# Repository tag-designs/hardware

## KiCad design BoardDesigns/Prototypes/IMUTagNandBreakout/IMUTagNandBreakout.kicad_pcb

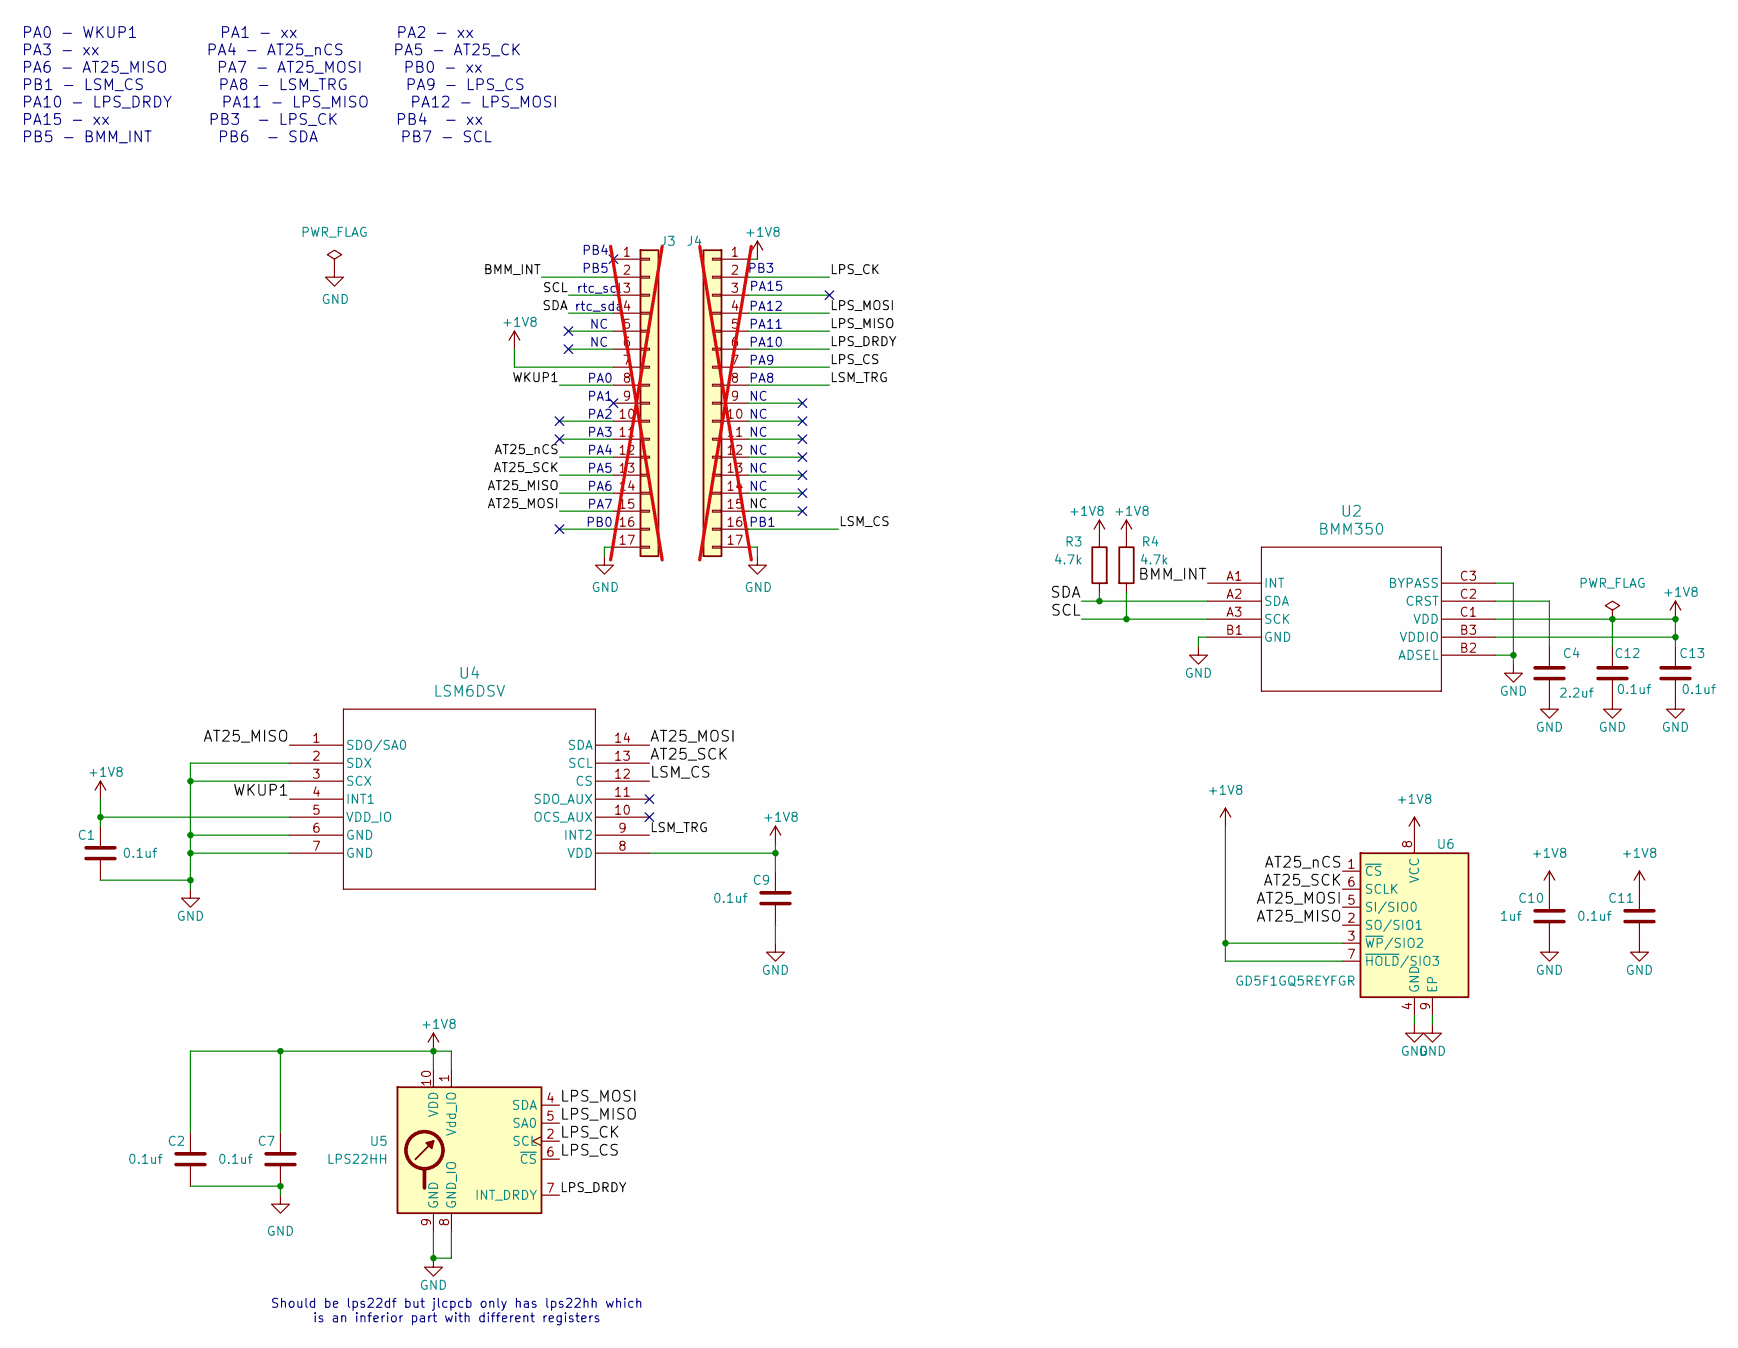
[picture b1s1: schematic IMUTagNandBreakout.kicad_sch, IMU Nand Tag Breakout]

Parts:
C1, C2, C7, C9, C11, C12, C13: 0.1uf; C_0603_1608Metric; MPN CC0603KRX7R9BB104; LCSC C14663
C4: 2.2uf; C_0603_1608Metric; MPN GRM188R61H225KE11D; LCSC C162273
C10: 1uf; C_0603_1608Metric; MPN CL10A105KB8NNNC; LCSC C15849
J3, J4: Conn_01x17; PinHeader_1x17_P2.54mm_Vertical_Staggered; not fitted
R3, R4: 4.7k; R_0603_1608Metric; MPN 0603WAF4701T5E; LCSC C23162
U2: BMM350; BGA9_BMM350_BOS; MPN BMM350; LCSC C17225907
U4: LSM6DSV; LGA14-L_2P59X3P1X0P5_STM; MPN LSM6DSV; LCSC C5267406
U5: LPS22HH; ST_HLGA-10_2x2mm_P0.5mm_LayoutBorder3x2y; MPN LPS22HH; LCSC C2827824
U6: GD5F1GQ5REYFGR; WSON-8-1EP_8x6mm_P1.27mm_EP3.4x4.3mm; MPN GD5F1GQ5REYFGR; LCSC C2976330

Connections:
+1V8: C1.1, C2.1, C7.1, C9.1, C10.1, C11.1, C12.1, C13.1, J3.7, J4.1, R3.1, R4.1, U2.B3 (VDDIO), U2.C1 (VDD), U4.5 (VDD_IO), U4.8 (VDD), U5.1 (Vdd_IO), U5.10 (VDD), U6.3 (~WP/SIO2), U6.7 (~HOLD/SIO3), U6.8 (VCC)
/AT25_MISO: J3.14, U4.1 (SDO/SA0), U6.2 (SO/SIO1)
/AT25_MOSI: J3.15, U4.14 (SDA), U6.5 (SI/SIO0)
/AT25_SCK: J3.13, U4.13 (SCL), U6.6 (SCLK)
/AT25_nCS: J3.12, U6.1 (~CS)
/BMM_INT: J3.2, U2.A1 (INT)
/LPS_CK: J4.2, U5.2 (SCL)
/LPS_CS: J4.7, U5.6 (~CS)
/LPS_DRDY: J4.6, U5.7 (INT_DRDY)
/LPS_MISO: J4.5, U5.5 (SA0)
/LPS_MOSI: J4.4, U5.4 (SDA)
/LSM_CS: J4.16, U4.12 (CS)
/LSM_TRG: J4.8, U4.9 (INT2)
/NC: J4.15
/SCL: J3.3, R4.2, U2.A3 (SCK)
/SDA: J3.4, R3.2, U2.A2 (SDA)
/WKUP1: J3.8, U4.4 (INT1)
GND: C1.2, C2.2, C4.2, C7.2, C9.2, C10.2, C11.2, C12.2, C13.2, J3.17, J4.17, U2.B1 (GND), U2.B2 (ADSEL), U2.C3 (BYPASS), U4.2 (SDX), U4.3 (SCX), U4.6 (GND), U4.7 (GND), U5.3 (GND), U5.8 (GND_IO), U5.9 (GND), U6.4 (GND), U6.9 (EP)
unnamed: C4.1, U2.C2 (CRST)

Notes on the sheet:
PA1
PA9
PA2
PA0
PA8
PA7
PA15
PA5
PA4
PB3
PA6
Should be lps22df but jlcpcb only has lps22hh which is an inferior part with different registers
PA3
PA0 - WKUP1 PA1 - xx PA2 - xx PA3 - xx PA4 - AT25_nCS PA5 - AT25_CK PA6 - AT25_MISO PA7 - AT25_MOSI PB0 - xx PB1 - LSM_CS PA8 - LSM_TRG PA9 - LPS_CS PA10 - LPS_DRDY PA11 - LPS_MISO PA12 - LPS_MOSI PA15 - xx PB3 - LPS_CK PB4 - xx PB5 - BMM_INT PB6 - SDA PB7 - SCL
PB4
PA12
PB0
PB5
PA10
rtc_sda
PA11
PB1
rtc_scl

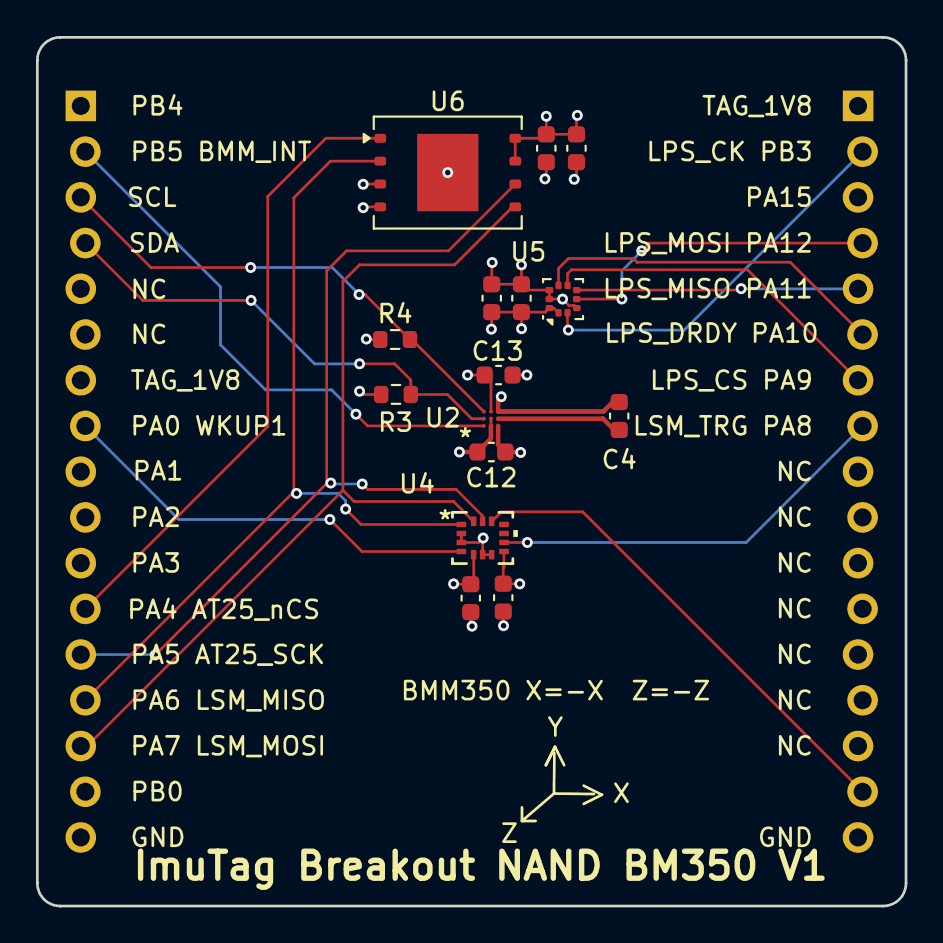
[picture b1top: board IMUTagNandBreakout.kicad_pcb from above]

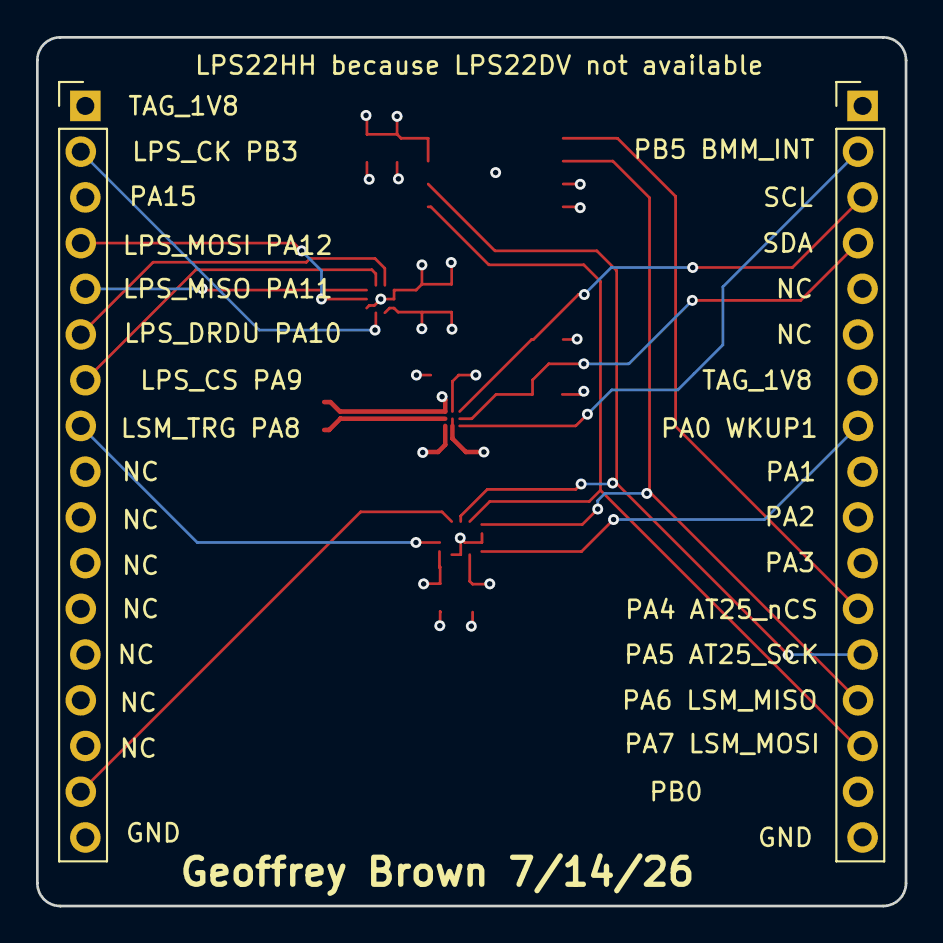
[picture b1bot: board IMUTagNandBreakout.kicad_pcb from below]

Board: 4 copper layers, 48.3 x 48.3 mm, 17 parts (2 on the bottom side), 18 nets.

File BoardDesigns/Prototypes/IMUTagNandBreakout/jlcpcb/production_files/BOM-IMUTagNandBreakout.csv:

Comment,Designator,Footprint,LCSC,Quantity
0.1uf,"C1,C11,C12,C13,C2,C7,C9",C_0603_1608Metric,C14663,7
1uf,C10,C_0603_1608Metric,C15849,1
2.2uf,C4,C_0603_1608Metric,C162273,1
4.7k,"R3,R4",R_0603_1608Metric,C23162,2
BMM350,U2,BGA9_BMM350_BOS,C17225907,1
GD5F1GQ5REYFGR,U6,WSON-8-1EP_8x6mm_P1.27mm_EP3.4x4.3mm,C2976330,1
LPS22HH,U5,ST_HLGA-10_2x2mm_P0.5mm_LayoutBorder3x2y,C2827824,1
LSM6DSV,U4,LGA14-L_2P59X3P1X0P5_STM,C5267406,1

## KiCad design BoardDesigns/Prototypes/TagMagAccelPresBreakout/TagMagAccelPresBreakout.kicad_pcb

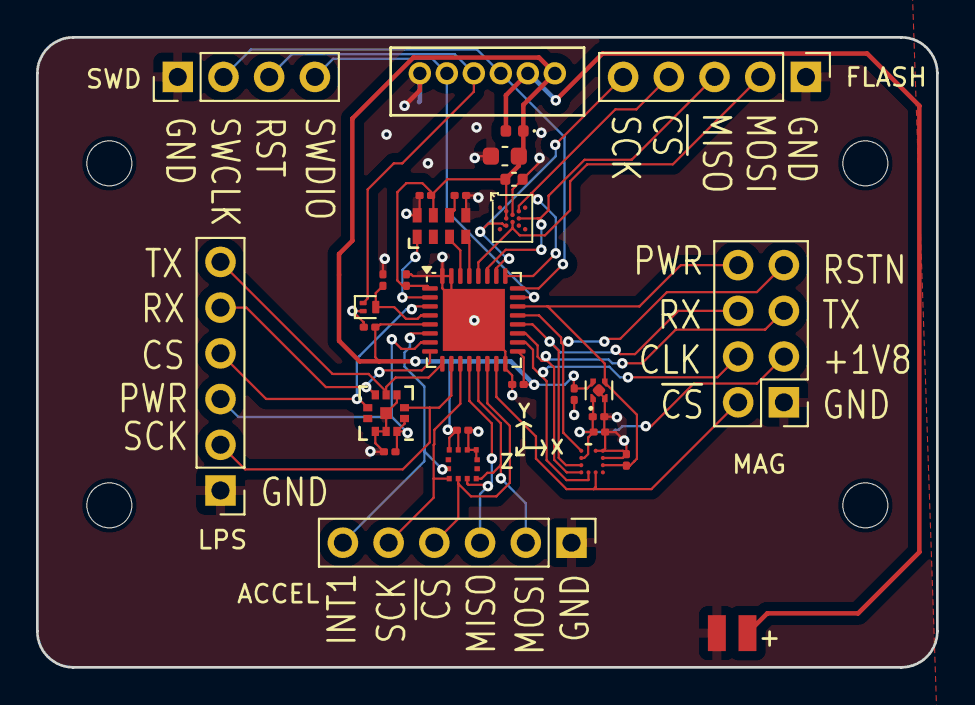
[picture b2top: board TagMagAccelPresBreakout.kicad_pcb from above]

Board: 2 copper layers, 50.0 x 35.0 mm, 34 parts (0 on the bottom side), 32 nets.

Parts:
C1, C2, C5, C6, C7, C501, C502, C503: 0.1uf; C_0201_0603Metric
C4: 47uf; C_0603_1608Metric
C8, C9, C101: 1uf; C_0201_0603Metric
C404: 22uf; C_0402_1005Metric
D401: D; D_0402_1005Metric
H1, H2, H3, H4: MountingHole; MountingHole_2.5mm
J1: Conn_01x06; CONN_B6B-ZR_JST
J2: Conn_01x04; PinHeader_1x05_P2.54mm_Vertical
J3: Conn_01x04; PinHeader_1x04_P2.54mm_Vertical
J4, J5: Conn_01x06; PinHeader_1x06_P2.54mm_Vertical
J6: Conn_02x04_Counter_Clockwise; PinHeader_2x04_P2.54mm_Vertical
J401: CONN_01X02; MS621
Q501: Q_NPN_BEC; SOT-883
R1: 10k; R_0201_0603Metric
U1: at25xe321D-UUN; adesto_wlcsp12
U2: LIS2DU12TR; LGA-12L_LIS2DU12_STM
U3: LPS27HHWTR
U4: AK09940A; AK09940a
U5: TPS7A2018PDQN; Texas_X2SON-4_1x1mm_P0.65mm
U302: stm32l431kc; QFN-32-1EP_5x5mm_P0.5mm_EP3.45x3.45mm
U501: RV-3028-C7; RV-8803-C7

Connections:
+1V8: C5.1, C9.1, J6.3, U4.C4 (VOD), U5.1 (OUT)
+2V5: C1.1, C2.1, C4.1, C8.1, C101.1, C404.1, C501.1, C503.1, D401.1 (K), J1.6, U1.B2 (VCC), U1.D2 (~RESET), U2.9 (VDD), U2.10 (VDD_IO), U5.4 (IN), U302.1 (VDD), U302.5 (VDDA/VREF+), U302.17 (VDD), U501.7 (VDD)
/AK_CS: J6.2, U4.A2 (CSB), U302.15 (PB1)
/AK_PWR: C7.1, J6.8, U4.B1 (VDD), U5.3 (EN), U302.22 (PA12)
/AK_RSTN: J6.7, U4.D4 (RSTN), U302.21 (PA11)
/AK_USART1_CK: J6.4, U4.A3 (SCL/SK), U302.18 (PA8)
/AK_USART1_RX: J6.6, U4.B4 (SO), U302.20 (PA10)
/AK_USART1_TX: J6.5, U4.A4 (SDA/SI), U302.19 (PA9)
/AT25_MISO: J2.3, U1.D4 (SO), U302.27 (PB4)
/AT25_MOSI: J2.2, U1.E3 (SI), U302.28 (PB5)
/AT25_SCK: J2.5, U1.F2 (SCK), U302.26 (PB3)
/AT25_nCS: J2.4, U1.B4 (nCS), U302.25 (PA15)
/LIS_CS: J4.4, U2.2 (CS), U302.14 (PB0)
/LIS_INT1: J4.6, U2.12 (INT1), U302.6 (PA0)
/LIS_MISO: J4.3, U2.3 (SDO/SA0), U302.12 (PA6)
/LIS_MOSI: J4.2, U2.4 (SDA/SDI/SDO), U302.13 (PA7)
/LIS_SCK: J4.5, U2.1 (SCL/SPC), U302.11 (PA5)
/LPS_CS: J5.4, U3.6 (CS), U302.3 (PC15)
/LPS_PWR: C6.1, J5.3, U3.1 (VDD_IO), U3.10 (VDD), U302.7 (PA1)
/LPS_RX: J5.5, U3.5 (SDO/SA0), U302.8 (PA2)
/LPS_SCK: J5.2, U3.2 (SCL/SPC), U302.10 (PA4)
/LPS_TX: J5.6, U3.4 (SDA/SDI/SDO), U302.9 (PA3)
/RST: J1.3, J3.3, Q501.1 (B)
/RTC_SCL: U302.30 (PB7), U501.3 (SCL)
/RTC_SDA: U302.29 (PB6), U501.4 (SDA)
/VBAT: D401.2 (A), J1.5, J401.1
/clkout: U302.2 (PC14), U501.1 (CLKOUT)
GND: C1.2, C2.2, C4.2, C5.2, C6.2, C7.2, C8.2, C9.2, C101.2, C404.2, C501.2, C502.2, C503.2, J1.1, J2.1, J3.1, J4.1, J5.1, J6.1, J401.2, Q501.2 (E), R1.2, U1.C3 (GND), U2.6 (GND), U2.7 (RES), U2.8 (GND), U3.3 (RES), U3.8 (GND), U3.9 (GND), U3.11 (GND), U4.C1 (VSS), U4.D1 (CAD0), U4.D2 (CAD1), U5.2 (GND), U5.5 (Pad), U302.16 (VSS), U302.31 (BOOT0), U302.32 (VSS), U302.33 (GND), U501.5 (GND), U501.8 (EVI)
unnamed: C502.1, Q501.3 (C), U302.4 (~NRST)
unnamed: R1.1, U501.6 (VBACK)
SWCLK: J1.4, J3.2, U302.24 (PA14)
SWDIO: J1.2, J3.4, U302.23 (PA13)

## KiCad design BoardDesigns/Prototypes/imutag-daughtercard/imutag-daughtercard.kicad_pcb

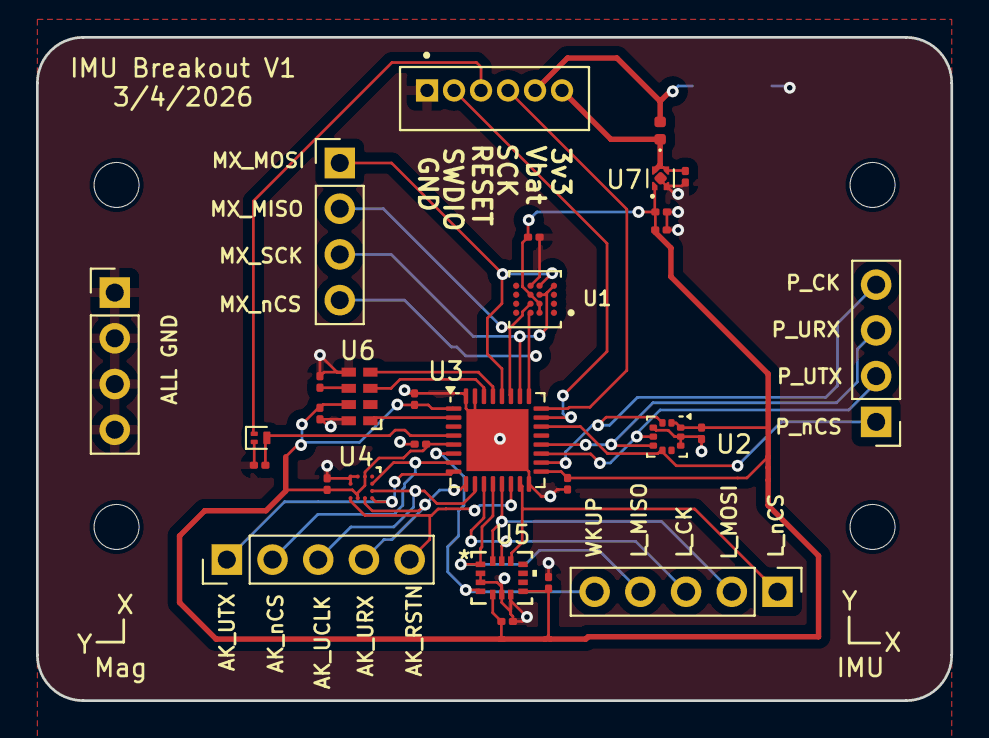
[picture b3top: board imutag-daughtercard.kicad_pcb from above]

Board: 2 copper layers, 50.8 x 36.9 mm, 34 parts (1 on the bottom side), 30 nets.

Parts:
C1, C2, C3, C4, C7, C8, C9, C10, C11, C12, C13: 0.1uf; C_0201_0603Metric
C5, C6: 1uf; C_0201_0603Metric
D1: D; D_0402_1005Metric
H1, H2, H3, H4: MountingHole; MountingHole_2.5mm
J1, J8: Conn_01x05; PinHeader_1x05_P2.54mm_Vertical
J2: Conn_01x06; JST_B6B-ZR_LF__SN_
J3: CONN_01X02; batterypads
J4, J6, J7: Conn_01x04; PinHeader_1x04_P2.54mm_Vertical
Q1: Q_NPN_BEC; SOT-883
R1: 10k; R_0201_0603Metric
U1: IC_MX25U12843GBBI00
U2: LPS22DF; ST_HLGA-10_2x2mm_P0.5mm_LayoutBorder3x2y
U3: stm32l431kc; QFN-32-1EP_5x5mm_P0.5mm_EP3.45x3.45mm
U4: AK09940A; AK09940a
U5: LSM6DSV; LGA14-L_2P59X3P1X0P5_STM
U6: RV-3028-C7; RV-8803-C7
U7: TPS7A2018PDQN; Texas_X2SON-4_1x1mm_P0.65mm

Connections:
+1V8: C2.1, C3.1, C4.1, C6.1, C7.1, C8.1, C9.1, C10.1, C11.1, C12.1, C13.1, U1.A2 (VCC), U1.B2 (~RESET), U1.C3 (~WP), U2.1 (Vdd_IO), U2.10 (VDD), U3.1 (VDD), U3.5 (VDDA/VREF+), U3.17 (VDD), U4.B1 (VDD), U4.C4 (VOD), U5.5 (VDD_IO), U5.8 (VDD), U6.7 (VDD), U7.1 (OUT)
/AK_CS: J8.2, U3.7 (PA1), U4.A2 (CSB)
/AK_RSTN: J8.5, U3.14 (PB0), U4.D4 (RSTN)
/AK_USART2_CK: J8.3, U3.10 (PA4), U4.A3 (SCL/SK)
/AK_USART2_RX: J8.4, U3.9 (PA3), U4.B4 (SO)
/AK_USART2_TX: J8.1, U3.8 (PA2), U4.A4 (SDA/SI)
/AT25_MISO: J4.2, U1.B3 (SO), U3.27 (PB4)
/AT25_MOSI: J4.1, U1.D2 (SI), U3.28 (PB5)
/AT25_SCK: J4.3, U1.C2 (SCLK), U1.D1, U3.26 (PB3)
/AT25_nCS: J4.4, U1.A3 (~CS), U3.25 (PA15)
/LPS_CS: J6.1, U2.6 (~CS), U3.22 (PA12)
/LSM_CK: J1.3, U3.11 (PA5), U5.13 (SCL)
/LSM_CS: J1.1, U3.15 (PB1), U5.12 (CS)
/LSM_MISO: J1.4, U3.12 (PA6), U5.1 (SDO/SA0)
/LSM_MOSI: J1.2, U3.13 (PA7), U5.14 (SDA)
/SCL: U3.30 (PB7), U6.3 (SCL)
/SDA: U3.29 (PB6), U6.4 (SDA)
/USART1_CK: J6.4, U2.2 (SCL), U3.18 (PA8)
/USART1_RX: J6.3, U2.5 (SA0), U3.20 (PA10)
/USART1_TX: J6.2, U2.4 (SDA), U3.19 (PA9)
/WKUP1: J1.5, U3.6 (PA0), U5.4 (INT1)
/clkout: U3.2 (PC14), U6.1 (CLKOUT)
GND: C1.2, C2.2, C3.2, C4.2, C5.2, C6.2, C7.2, C8.2, C9.2, C10.2, C11.2, C12.2, C13.2, J2.1, J3.2, J7.1, J7.2, J7.3, J7.4, Q1.2 (E), R1.2, U1.D3 (GND), U2.3 (GND), U2.8 (GND_IO), U2.9 (GND), U3.16 (VSS), U3.31 (BOOT0), U3.32 (VSS), U3.33 (GND), U4.C1 (VSS), U4.D1 (CAD0), U4.D2 (CAD1), U5.2 (SDX), U5.3 (SCX), U5.6 (GND), U5.7 (GND), U6.5 (GND), U6.8 (EVI), U7.2 (GND), U7.5 (Pad)
unnamed: C1.1, Q1.3 (C), U3.4 (~NRST)
unnamed: R1.1, U6.6 (VBACK)
RST: J2.3, Q1.1 (B)
SWCLK: J2.4, U3.24 (PA14)
SWDIO: J2.2, U3.23 (PA13)
VBAT: D1.2 (A), J2.5, J3.1
VIN: C5.1, D1.1 (K), J2.6, U7.3 (EN), U7.4 (IN)

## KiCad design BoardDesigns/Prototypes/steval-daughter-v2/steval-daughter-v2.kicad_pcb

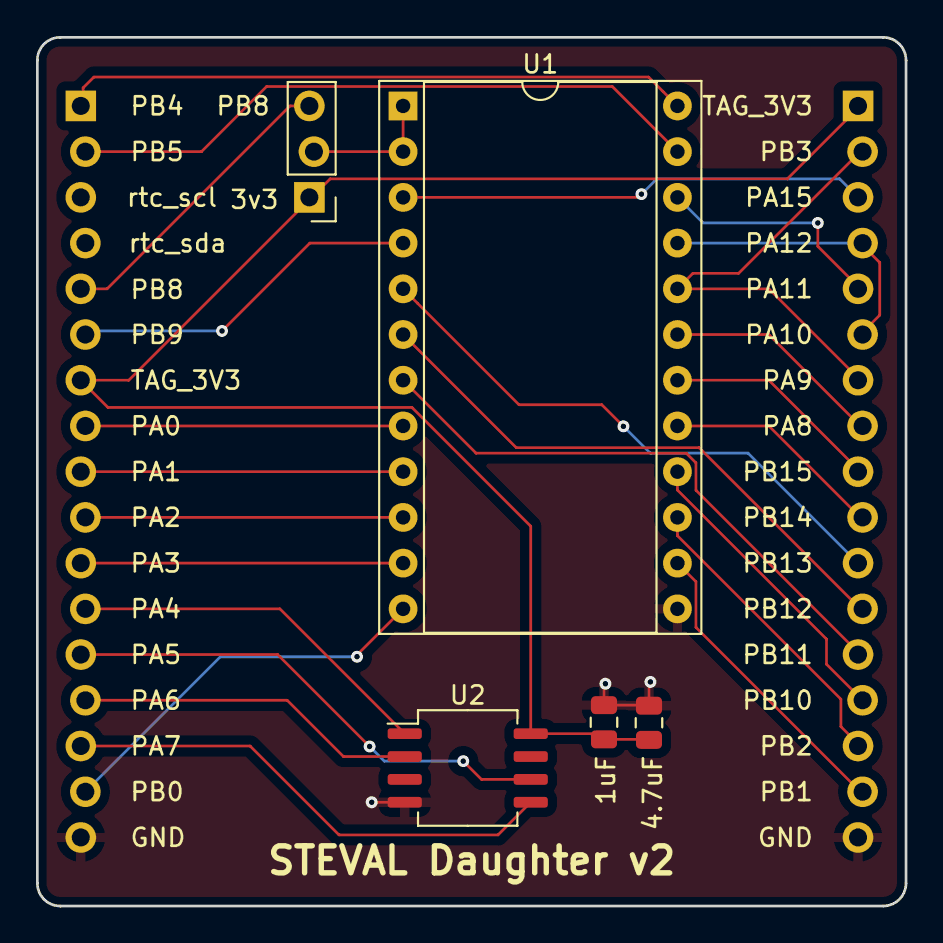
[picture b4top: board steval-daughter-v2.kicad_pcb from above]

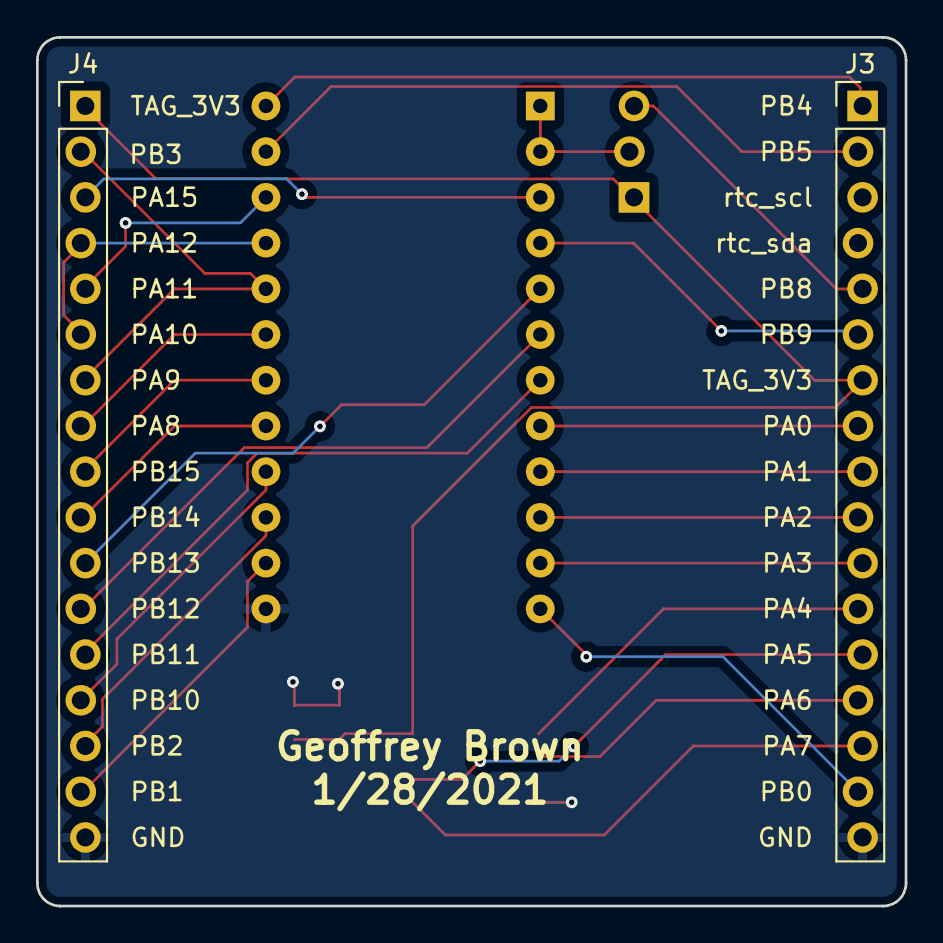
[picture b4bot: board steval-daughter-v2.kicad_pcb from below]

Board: 2 copper layers, 48.3 x 48.3 mm, 7 parts (2 on the bottom side), 29 nets.

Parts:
C1: 4.7uF; C_0805_2012Metric
C2: 1uF; C_0805_2012Metric
J3, J4: Conn_01x17; PinHeader_1x17_P2.54mm_Vertical_Staggered
J101: Conn_01x03; PinHeader_1x03_P2.54mm_Vertical
U1: ST-Steval; DIP-24_W15.24mm_Socket
U2: AT25FF321; SO-8_5.3x6.2mm_P1.27mm

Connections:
/PA0: J3.8, U1.8
/PA1: J3.9, U1.9
/PA2: J3.10, U1.10
/PA3: J3.11, U1.11
/PA4: J3.12, U2.1
/PA5: J3.13, U2.6
/PA6: J3.14, U2.2
/PA7: J3.15, U2.5
/PA8: J4.8, U1.19
/PA9: J4.2, J4.7, U1.20
/PA10: J4.4, J4.6, U1.21
/PA11: J4.5, U1.22
/PA15: J4.3, U1.3
/PB0: J3.16, U1.12
/PB1: J4.16, U1.14
/PB2: J4.15, U1.15
/PB4: J3.1, U1.24
/PB5: J3.2, U1.23
/PB8: J3.5, J101.3
/PB9: J3.6, U1.4
/PB10: J4.14, U1.16
/PB11: J4.13, U1.7
/PB12: J4.12, U1.6
/PB13: J4.11, U1.5
/PB14: J4.10, U1.17
/PB15: J4.9, U1.18
/TAG_3V3: C1.1, C2.1, J3.7, J4.1, J101.1, U2.8
GND: C1.2, C2.2, J3.17, J4.17, U1.13, U2.4
unnamed: J101.2, U1.1, U1.2

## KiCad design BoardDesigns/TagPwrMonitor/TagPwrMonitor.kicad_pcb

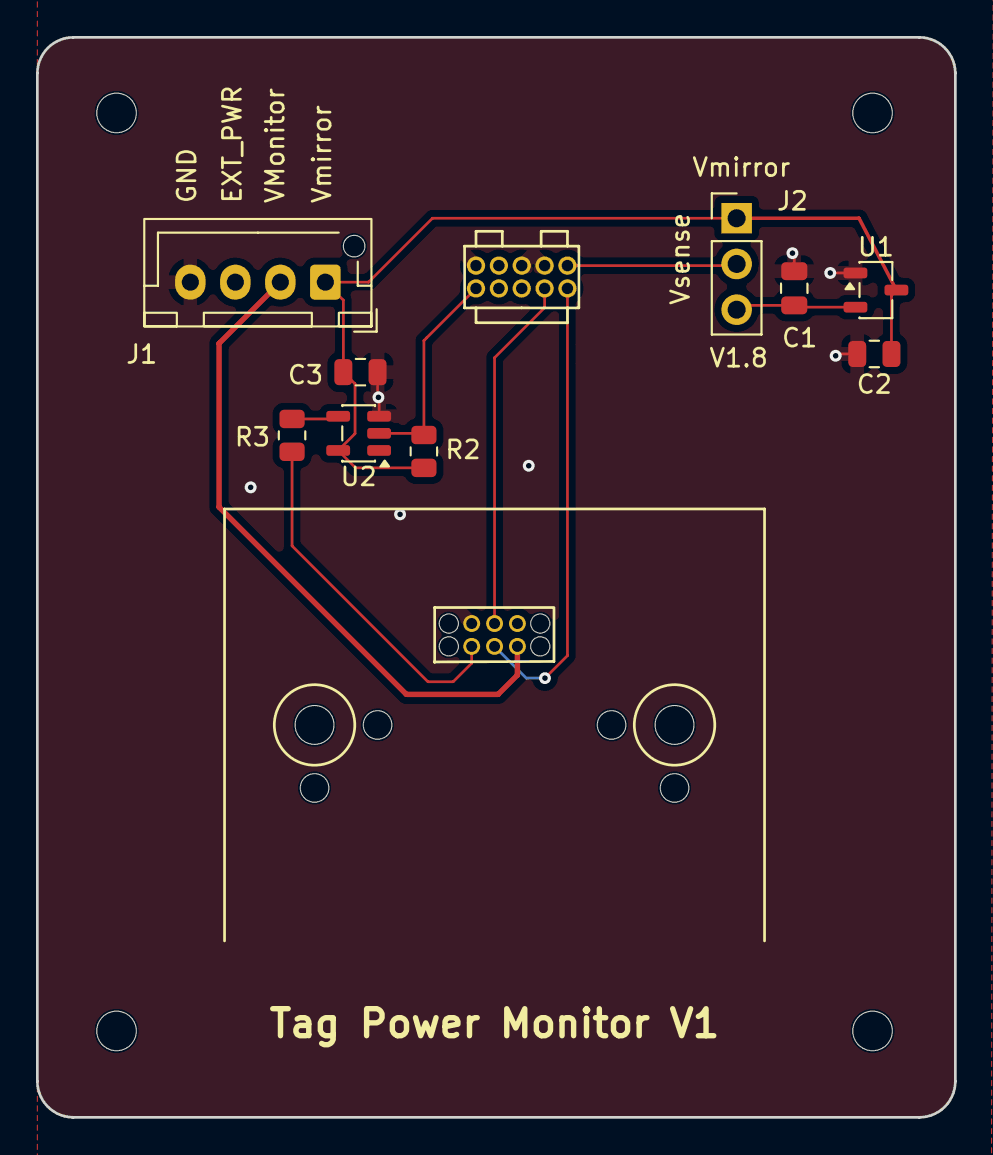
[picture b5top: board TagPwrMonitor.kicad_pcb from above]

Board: 2 copper layers, 51.0 x 60.0 mm, 15 parts (0 on the bottom side), 10 nets.

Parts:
C1, C2: 1uf; C_0805_2012Metric
C3: 100nf; C_0805_2012Metric
H1, H2, H3, H4: MountingHole_2.2mm_M2
J1: JST XH_B4B-XH; JST_XH_B4B-XH-AM_1x04_P2.50mm_Vertical
J2: Conn_01x03; PinHeader_1x03_P2.54mm_Vertical
J101: Conn_02x03_Odd_Even; 6pin_tagpoints_double_screws
J102: swd connector; FTSH-105-01-F-D-K
R2: 10k; R_0805_2012Metric
R3: 1k; R_0805_2012Metric
U1: XC6206PxxxMR; SOT-23-3
U2: SN74LV1T04DBVR; SOT-23-5

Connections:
/NRST: J102.10, R2.1, U2.2 (A)
/STLINK_VSENSE: J2.2, J102.1
/TAG_3V3: J1.2, J101.5
/TAG_MIRROR: C2.1, C3.1, J1.1, J2.1, R2.2, U1.3 (VI), U2.5 (VCC)
/TAG_RESET: J101.1, R3.1
/TAG_SCK: J101.4, J102.4
/TAG_SWDIO: J101.3, J102.2
GND: C1.2, C2.2, C3.2, J1.4, J101.2, J102.3, J102.5, J102.9, U1.1 (GND), U2.3 (GND)
unnamed: C1.1, J2.3, U1.2 (VO)
unnamed: R3.2, U2.4 (Y)

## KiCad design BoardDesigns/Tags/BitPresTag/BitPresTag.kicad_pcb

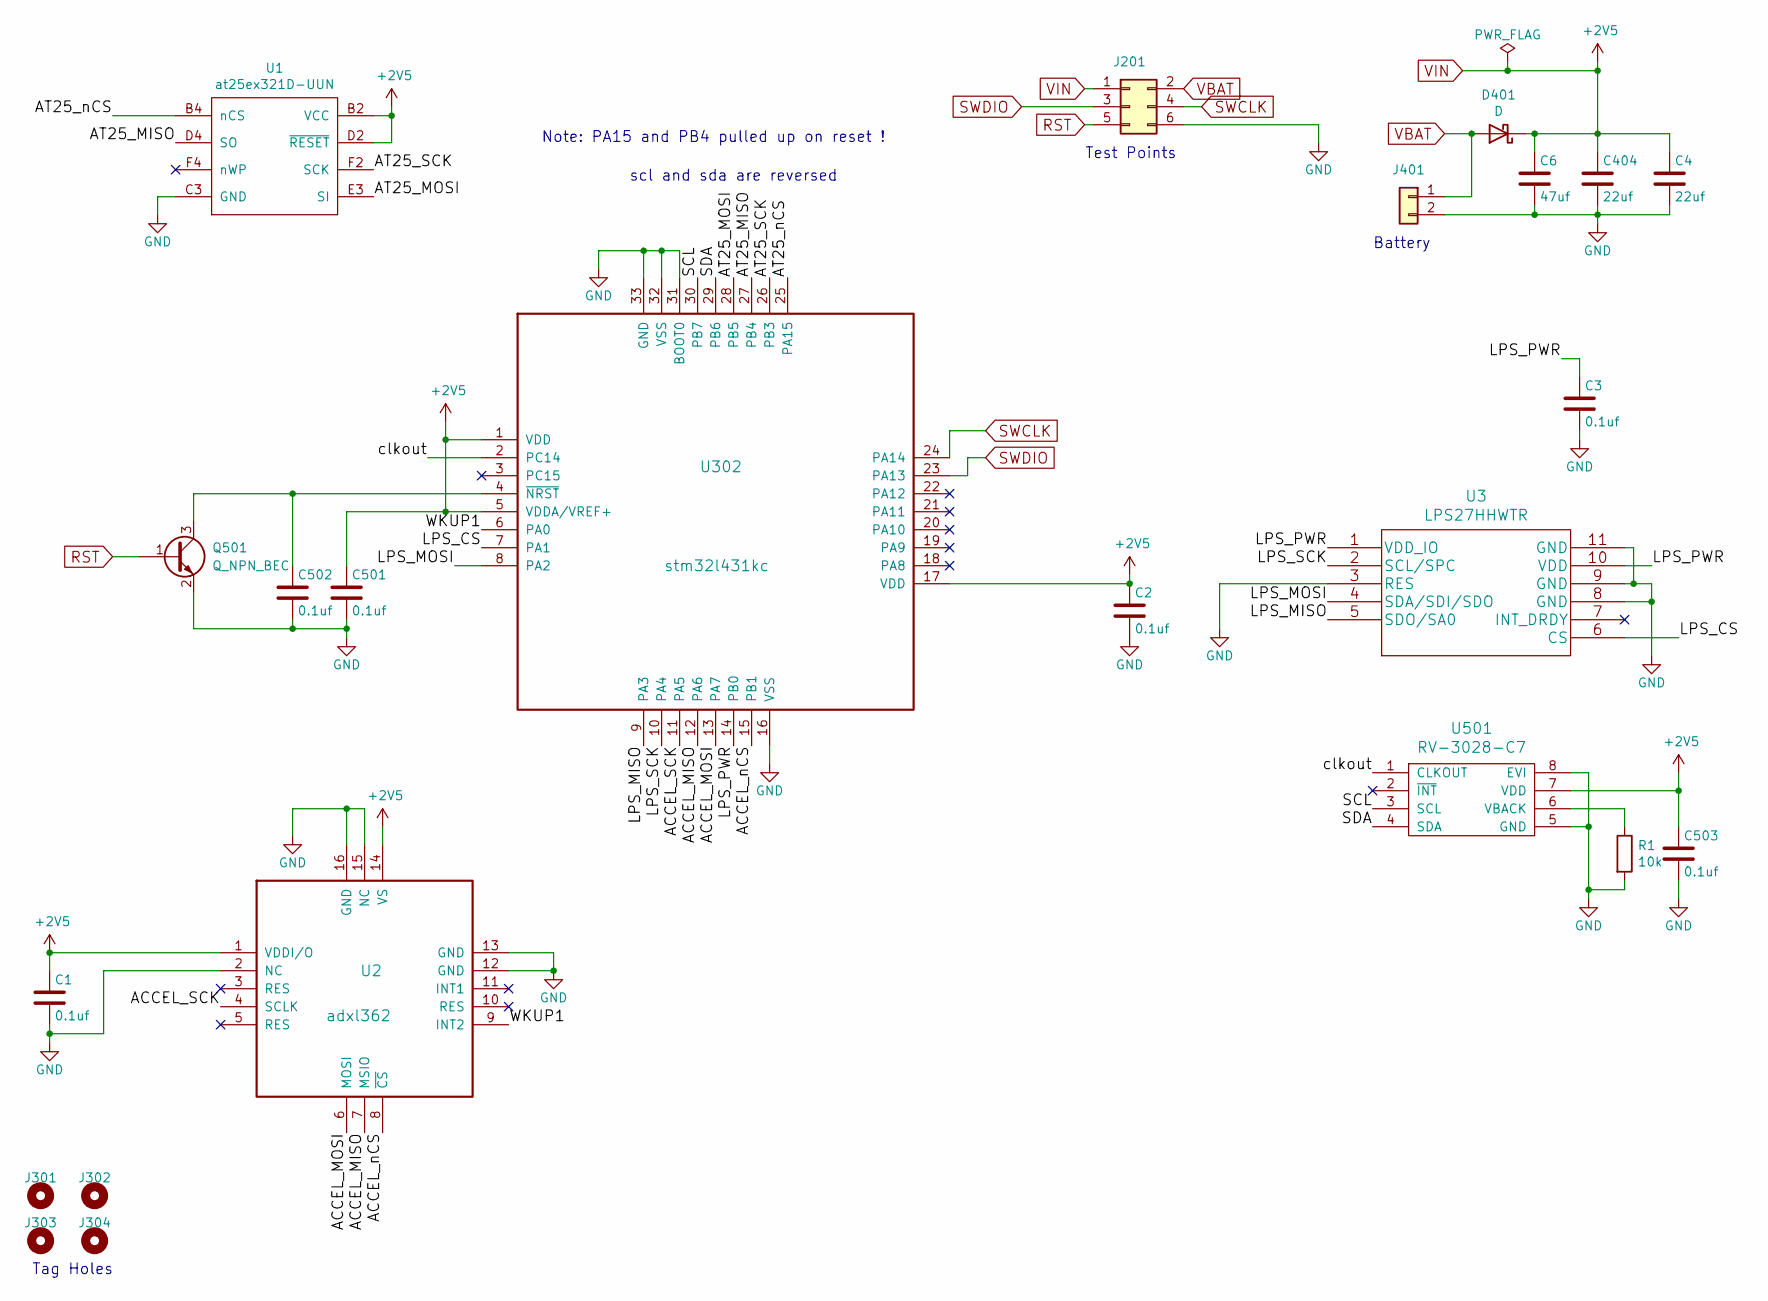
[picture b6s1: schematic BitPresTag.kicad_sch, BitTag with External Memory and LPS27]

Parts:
C1: 0.1uf; C_0201_0603Metric; MPN CL05F104ZO5NNNC
C2: 0.1uf; C_0201_0603Metric; MPN GRM033R60J105MEA2D; LCSC C76929
C3: 0.1uf; C_0201_0603Metric; MPN GRM033C81E104KE14D
C4, C404: 22uf; C_0402_1005Metric; MPN 04026D226MAT2A; LCSC C2179118
C6: 47uf; C_0603_1608Metric; MPN 06036D476MAT2A
C501, C502, C503: 0.1uf; C_0201_0603Metric; MPN C181047; LCSC C181047
D401: D; D_0402_1005Metric; MPN CDBQC0130L-HF; LCSC C2886012
J201: CONN_02X04; tagpoints6
J301, J302, J303, J304: Conn_01x01; taghole1.1mm
J401: CONN_01X02; MS621
Q501: Q_NPN_BEC; SOT-883; MPN BC847AMB,315; LCSC C686658
R1: 10k; R_0201_0603Metric; MPN RC0201FR-0710KL; LCSC C106225
U1: at25ex321D-UUN; adesto_wlcsp12; MPN AT25FF321A-UUN-T; LCSC C1858339
U2: adxl362; ADXL362; MPN ADXL362BCCZ-RL7
U3: LPS27HHWTR; MPN LPS27HHTWTR
U302: stm32l431kc; QFN-32-1EP_5x5mm_P0.5mm_EP3.45x3.45mm; MPN STM32L432KCU6; LCSC C1337280
U501: RV-3028-C7; RV-8803-C7; MPN RV-3028-C7 32.768KHZ 1PPM-TA-QA; LCSC C3019759

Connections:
/ACCEL_MISO: U2.7 (MSIO), U302.12 (PA6)
/ACCEL_MOSI: U2.6 (MOSI), U302.13 (PA7)
/ACCEL_SCK: U2.4 (SCLK), U302.11 (PA5)
/ACCEL_nCS: U2.8 (~CS), U302.15 (PB1)
/AT25_MISO: U1.D4 (SO), U302.27 (PB4)
/AT25_MOSI: U1.E3 (SI), U302.28 (PB5)
/AT25_SCK: U1.F2 (SCK), U302.26 (PB3)
/AT25_nCS: U1.B4 (nCS), U302.25 (PA15)
/LPS_CS: U3.6 (CS), U302.7 (PA1)
/LPS_MISO: U3.5 (SDO/SA0), U302.9 (PA3)
/LPS_MOSI: U3.4 (SDA/SDI/SDO), U302.8 (PA2)
/LPS_PWR: C3.1, U3.1 (VDD_IO), U3.10 (VDD), U302.14 (PB0)
/LPS_SCK: U3.2 (SCL/SPC), U302.10 (PA4)
/SCL: U302.30 (PB7), U501.3 (SCL)
/SDA: U302.29 (PB6), U501.4 (SDA)
/WKUP1: U2.9 (INT2), U302.6 (PA0)
/clkout: U302.2 (PC14), U501.1 (CLKOUT)
GND: C1.2, C2.2, C3.2, C4.2, C6.2, C404.2, C501.2, C502.2, C503.2, J201.6, J401.2, Q501.2 (E), R1.2, U1.C3 (GND), U2.2 (NC), U2.12 (GND), U2.13 (GND), U2.15 (NC), U2.16 (GND), U3.3 (RES), U3.8 (GND), U3.9 (GND), U3.11 (GND), U302.16 (VSS), U302.31 (BOOT0), U302.32 (VSS), U302.33 (GND), U501.5 (GND), U501.8 (EVI)
unnamed: C502.1, Q501.3 (C), U302.4 (~NRST)
unnamed: R1.1, U501.6 (VBACK)
RST: J201.5, Q501.1 (B)
SWCLK: J201.4, U302.24 (PA14)
SWDIO: J201.3, U302.23 (PA13)
VBAT: D401.2 (A), J201.2, J401.1
VIN: C1.1, C2.1, C4.1, C6.1, C404.1, C501.1, C503.1, D401.1 (K), J201.1, U1.B2 (VCC), U1.D2 (~RESET), U2.1 (VDDI/O), U2.14 (VS), U302.1 (VDD), U302.5 (VDDA/VREF+), U302.17 (VDD), U501.7 (VDD)

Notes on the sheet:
Note: PA15 and PB4 pulled up on reset !
Tag Holes
Test Points
scl and sda are reversed
Battery

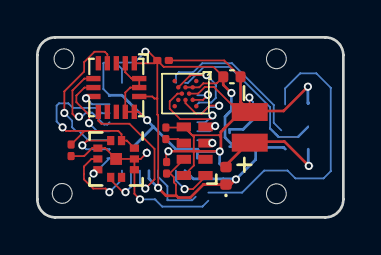
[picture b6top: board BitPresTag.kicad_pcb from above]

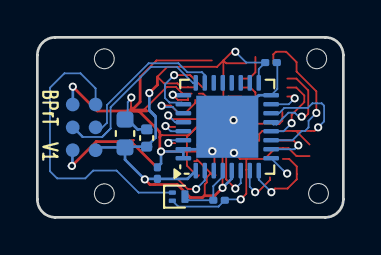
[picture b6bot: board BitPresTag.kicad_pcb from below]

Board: 2 copper layers, 17.0 x 10.0 mm, 23 parts (8 on the bottom side), 25 nets.

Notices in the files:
parts and their libraries:
Copyright 2016 Accelerated Designs. All rights reserved.
